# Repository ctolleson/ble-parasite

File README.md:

# b-parasite

## Plant monitor KiCad projects

These are two independent hardware designs. Each has its own `.kicad_pro`, `.kicad_sch`, `.kicad_pcb`, and project libraries.

| Design | KiCad project | Git branch |
| --- | --- | --- |
| **BLE module — Raytac MDBT50Q-1MV2** | [kicad-raytac-plant-monitor/parasite.kicad_pro](kicad-raytac-plant-monitor/parasite.kicad_pro) | `feature-raytac-module-plant-monitor` |
| **Bare MCU — nRF52840-QIAA, AQFN-73** | [kicad-bare-nrf52840/parasite.kicad_pro](https://github.com/ctolleson/ble-parasite/blob/feature-nrf52840-bare-mcu-plant-monitor/kicad-bare-nrf52840/parasite.kicad_pro) | `feature-nrf52840-bare-mcu-plant-monitor` |

The module revision uses 0805 ordinary passives and a 30 mm straight-sided PCB. The bare-MCU project is preserved independently on its branch and in its original checkout. Both use the historical filename `parasite`; identify them by their project directory. The module conversion did not replace the bare-MCU schematic or PCB. The upstream `kicad/` directory below is historical b-parasite reference hardware, not either customized project above.

b-parasite is an open source soil moisture and ambient temperature/humidity/light sensor.

# Features
* Capacitive Soil moisture sensor - see [this blog post](https://rbaron.net/blog/2021/04/05/How-capacitive-soil-moisture-sensors-work.html), [this Twitter thread](https://twitter.com/rbaron_/status/1367182806368071685), and [this post](https://wemakethings.net/2012/09/26/capacitance_measurement/) for nice resources on how they work
* Air temperature and humidity sensor using a [Sensirion's SHTC3](https://sensirion.com/media/documents/643F9C8E/63A5A436/Datasheet_SHTC3.pdf)
* Light sensor using an [ALS-PT19](https://en.everlight.com/wp-content/plugins/ItemRelationship/product_files/pdf/ALS-PT19-315C-L177-TR8_V8.pdf) phototransistor
* Powered by a common CR2032 coin cell, potentially for over two years
* Support for [nRF52840](https://www.nordicsemi.com/products/nrf52840) and [nRF52833](https://www.nordicsemi.com/products/nrf52833) modules
* Open hardware and open source design

# Software
This repository also hosts a few different firmware samples for b-parasite.

|Sample|Description|Extra Documentation|
|---|---|---|
|[samples/ble](./code/samples/ble)|This is the most battle-tested and useful firmware. It periodically reads all sensors and broadcast them via Bluetooth Low Energy (BLE). It works with [Home Assistant](https://www.home-assistant.io/) + [BTHome](https://bthome.io/) out of the box. |[Docs](./code/samples/ble/README.md)|
|[samples/zigbee](./code/samples/zigbee)| An experimental/educational/exploratory basic Zigbee sample built on [nRF Connect + ZBOSS](https://developer.nordicsemi.com/nRF_Connect_SDK/doc/latest/nrf/ug_zigbee.html). It integrates with [Home Assistant](https://www.home-assistant.io/) via [ZHA](https://www.home-assistant.io/integrations/zha) or [Zigbee2MQTT](https://www.zigbee2mqtt.io/). |[Docs](./code/samples/zigbee/README.md)|
|[samples/blinky](./code/samples/blinky)| The classic "Hello, world" |-|
|[samples/soil-read-loop](./code/samples/soil-read-loop)| Reads the soil moisture sensor on a loop. Useful for experimenting and calibrating the sensor. |-|
|[samples/input](./code/samples/input)| Handles button presses. Useful for power profiling GPIO interrupts and testing debouncing for push switches on [boards that have them](https://github.com/rbaron/b-parasite/wiki/Hardware-Versions). |-|

# Documentation
Information about how to order, assemble, build the samples, protect the sensor and flash the firmware is on [the Wiki](https://github.com/rbaron/b-parasite/wiki).

# Repository Organization
* [code/](./code/) - A [`west workspace`](https://docs.zephyrproject.org/latest/develop/west/workspaces.html) containing the common `prstlib` module library and samples, built with Nordic's [nRF Connect SDK](https://www.nordicsemi.com/Products/Development-software/nrf-connect-sdk).
* [kicad/](./kicad/) - KiCad schematic, layout and fabrication files for the printed circuit board (PCB)
* [data/](data/) - data for testing and sensor calibration
* [bridge/](bridge/) - an [ESPHome](https://github.com/esphome/esphome)-based BLE-MQTT bridge
* [case/](case/) - a 3D printable case

# Case

We have three different 3D-printable cases:
1. Original snap-on case - [case/Top.stl](./case/Top.stl), [case/Bottom.stl](./case/Bottom.stl)
2. High airflow - [case/b_parasite_case_high_airflow.stl](./case/b_parasite_case_high_airflow.stl)
3. Mushroom-style - available on [Printables](https://www.printables.com/model/456571-mushroomcap-for-b-parasite-soil-moisture-sensor)
4. b-parasite Hat - available on [Printables](https://www.printables.com/model/901220-waterproof-case-for-b-parasite-soil-moisture-air-s)

# Accessories

Designs and hardware to help you, when building your own:
1. Desk holder for b-parasites [Printables](https://www.printables.com/de/model/566974-b-parasite-holder)

# License
The hardware and associated design files are released under the [Creative Commons CC BY-SA 4.0 license](https://creativecommons.org/licenses/by-sa/4.0/).
The code is released under the [MIT license](https://opensource.org/licenses/MIT).

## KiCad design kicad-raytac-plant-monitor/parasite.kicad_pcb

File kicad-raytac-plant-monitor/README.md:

# Raytac nRF52840 plant monitor — MODULE-B

Independent KiCad project using Raytac MDBT50Q-1MV2 with its integrated chip antenna. Open `parasite.kicad_pro` in KiCad 10. The prior bare-MCU design remains in its original branch.

## Interfaces

- **J1:** 2 × 5, 1.27 mm Cortex SWD header for a J-Link probe or compatible adapter. Pin 1: target +3V0/VTref; 2: SWDIO; 3: GND; 4: SWDCLK; 5: GND; 6: SWO (P1.00); 7: NC/key; 8: NC; 9: GND detect; 10: nRESET. Power the target from its battery; VTref is a voltage reference, not a probe power input. Check cable orientation against pin 1 before connecting. Header pin 7 is electrically unused; remove it if required by a keyed cable.
- **J2:** 1 × 4, 2.54 mm I2C expansion header. Pins 1–4: +3V0, GND, SDA/P0.24, SCL/P0.13. Shared with the SHTC3 and existing 10 kΩ pull-ups. Use short wiring and do not apply 5 V.
- **J3:** 1 × 2, 2.54 mm external NFC antenna header. Pin 1: NFC1/P0.09; pin 2: NFC2/P0.10. An external antenna and matching/tuning appropriate to its inductance are required. The module's chip antenna is for 2.4 GHz BLE, not NFC.

## Hardware

- CR2032 supply; module VDD and VDDH share +3V0, REG0 bypassed. DCCH is unused. VBUS is grounded and USB data pins are unused, following Raytac's no-USB application circuit.
- Module contains the 32 MHz crystal, RF matching and regulator inductors. External 32.768 kHz crystal retained.
- All seven ordinary host resistors, all six capacitors and D2 use standard imperial **0805** (2.0 × 1.25 mm nominal bodies). The Raytac module, sensors, crystal, diode, transistor, switches and connectors retain their required packages. Values are preserved; 0805 manufacturer part numbers and electrical ratings are recorded in the schematic and PCB fields. Inventory has not been rechecked for this revision.
- **30.0 × 126.4 mm** board with straight, parallel vertical sides and a 45° tapered bottom tip inspired by the original b-parasite. Components are above the soil limit; the CR2032 holder is on the back.
- Four copper layers; 0.15 mm minimum signal width, 0.125 mm clearance, ordinary through vias with 0.60 mm copper / 0.30 mm drill. No blind/buried vias or microvias.
- Antenna at the top board edge with an all-layer copper/tracks/vias keepout across the head. Keep metal, the battery, cables and enclosure hardware away from the antenna.
- Soil probe electrode and surrounding ground remain covered by solder mask. A GND through via near the tip connects the front and back probe ground pours.

## Validation status

KiCad 10 native ERC: **0 violations**. Native DRC: **0 violations, 0 unconnected items**. Independent comparison of the native schematic netlist and saved PCB: **133/133 pad nets match**, including all 40 intentional no-connect pads. Saved reports and previews are in `review/`.

MCP PCB quality gate passes. Other MCP heuristics flag native no-connect net names, wire-interior pin joins, opposing-side placement and module-center-to-cap distance; these are reviewed in `review/REVIEW.md`. They are not represented as blanket gate passes.

**Manufacturing status: needs engineering review; not a manufacturing release.** Select exact connector SKUs and confirm their land patterns/cable fit before procurement. J1 currently uses KiCad’s generic 2×5 1.27 mm SMT pin-header footprint. Check the assembly process for the module and underside battery holder. A new manufacturing package and quotation are needed for this revision. Firmware must use the new GPIO assignments and configure NFC/SWO as required. Verify soil calibration, sensor behavior, sleep current, crystal start-up, BLE range and NFC antenna tuning on hardware.

## References

- [Raytac module specification](https://www.raytac.com/tw/download/index.php?index_id=24)
- [Nordic nRF52840 pin assignments](https://docs.nordicsemi.com/r/bundle/ps_nrf52840/page/pin.html)

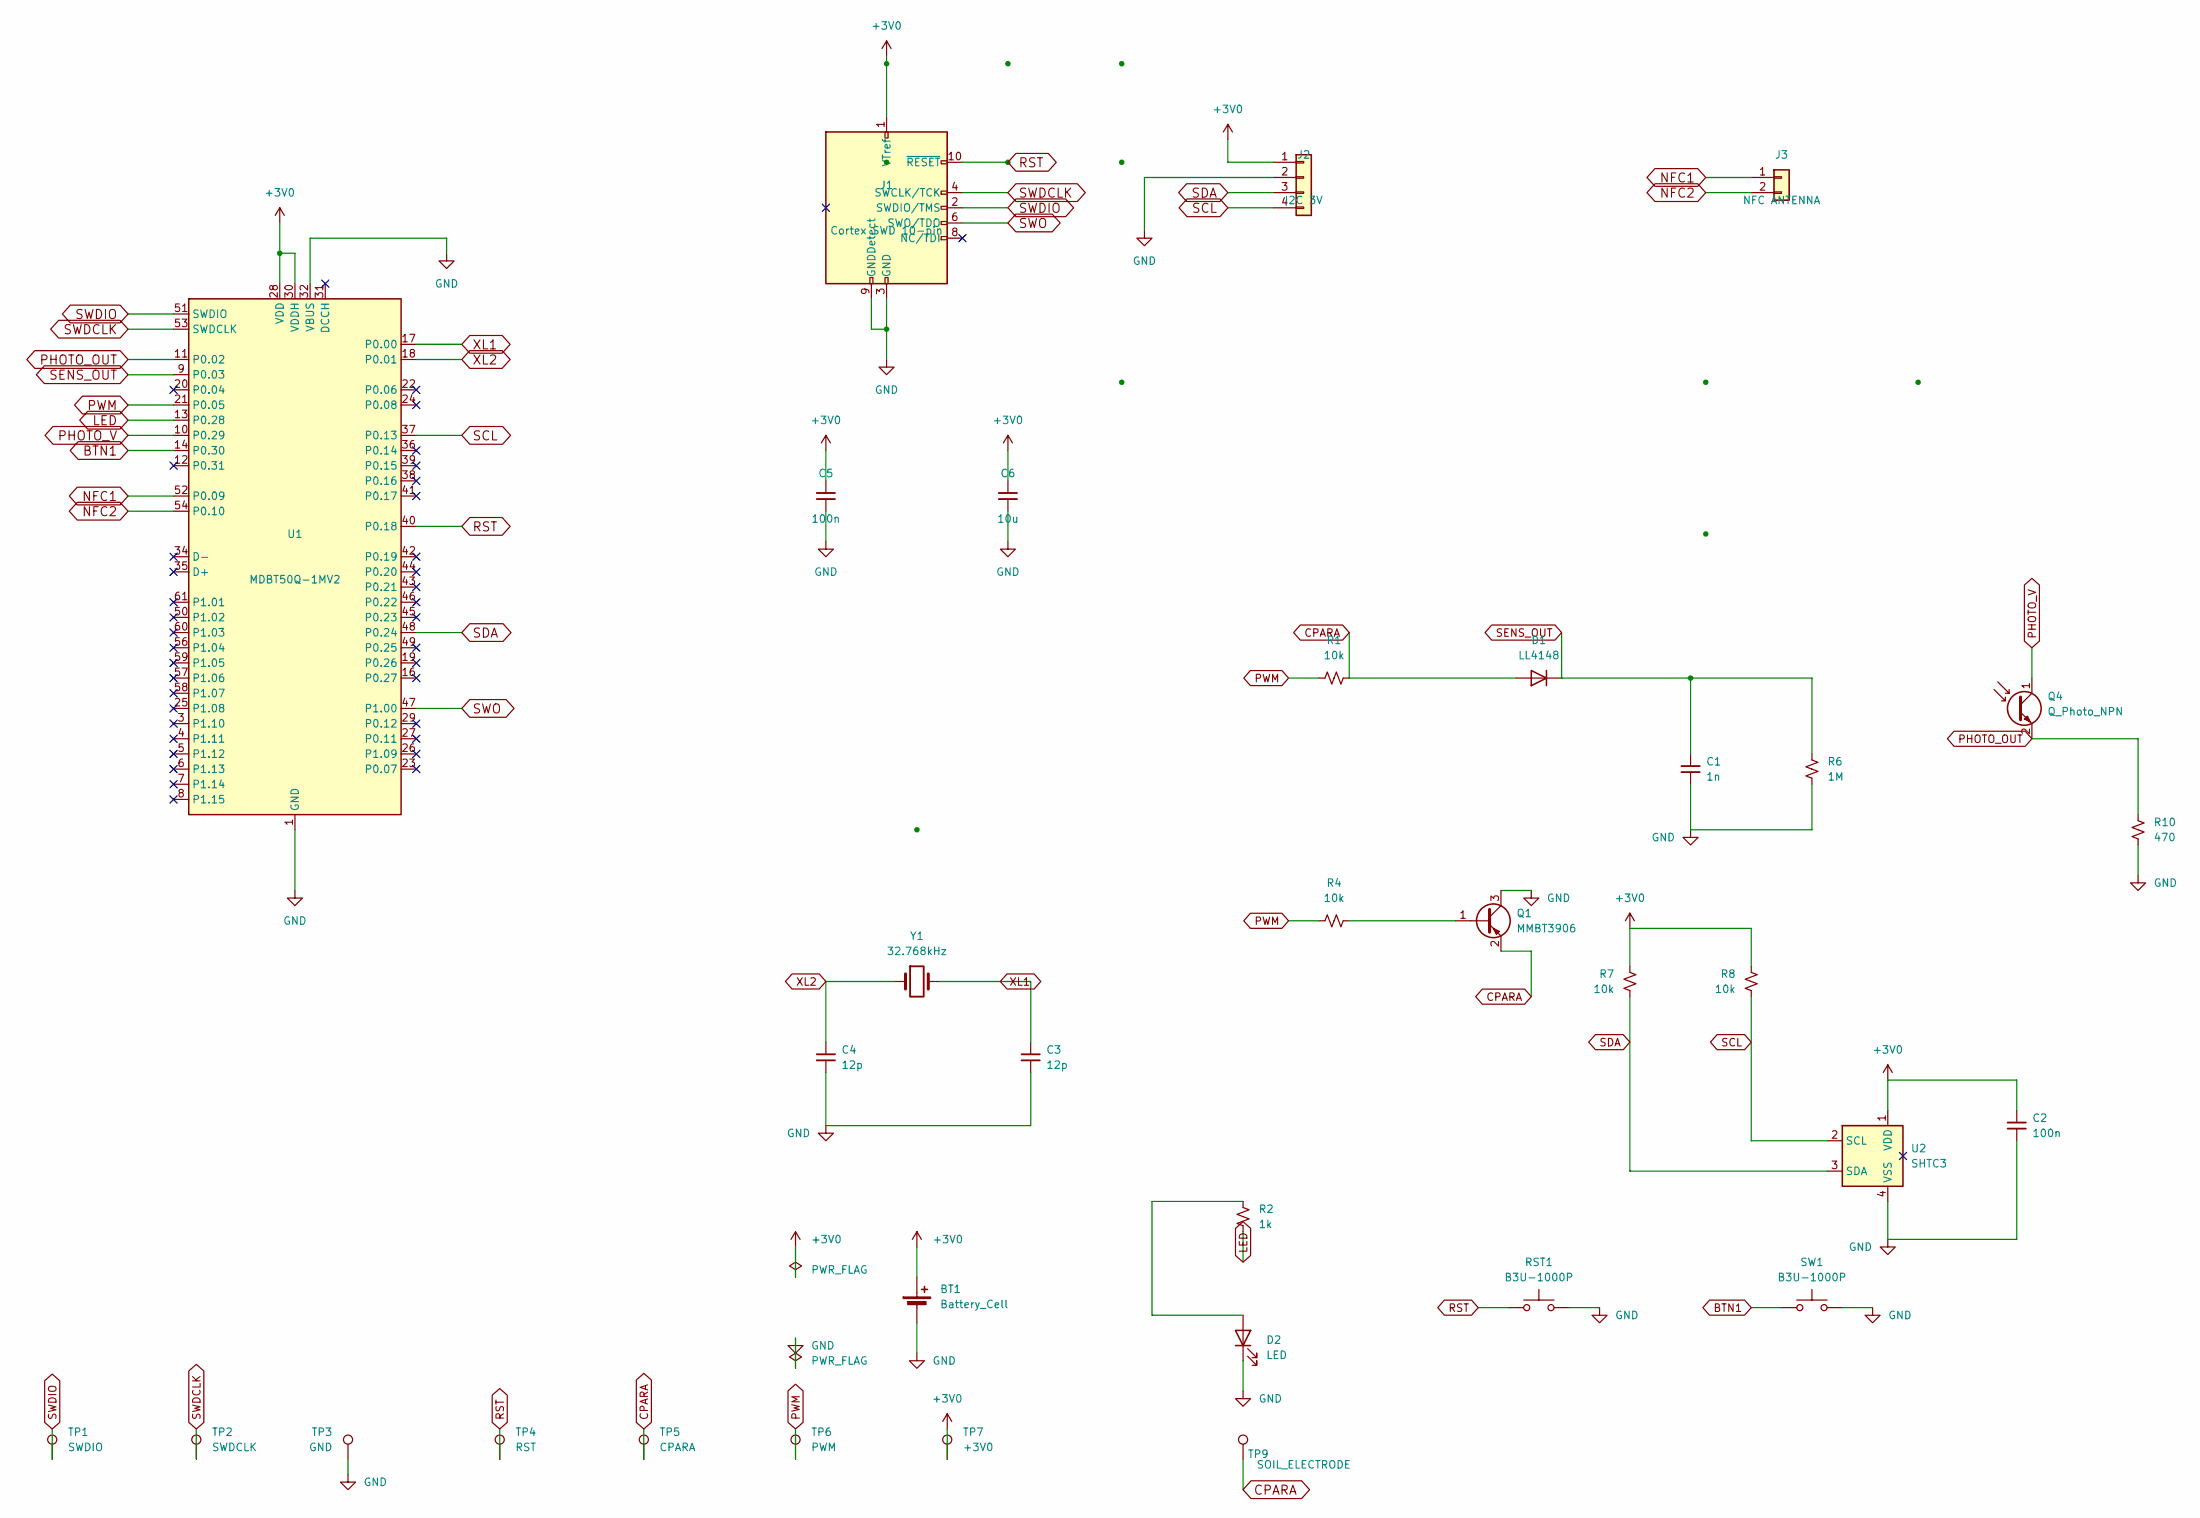
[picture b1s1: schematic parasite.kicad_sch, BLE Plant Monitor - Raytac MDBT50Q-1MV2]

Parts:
BT1: Battery_Cell; BatteryHolder_Keystone_1060_NoBodySilk; MPN 1060; LCSC C5370859
C1: 1n; C_0805_2012Metric; Voltage 50V; MPN C0805C102J5GACTU
C2, C5: 100n; C_0805_2012Metric; Voltage 50V; MPN C0805C104K5RACTU
C3, C4: 12p; C_0805_2012Metric; Voltage 50V; MPN C0805C120J5GACTU
C6: 10u; C_0805_2012Metric; Voltage 16V; MPN GRM21BR61C106KE15L
D1: LL4148; D_MiniMELF; MPN LL4148; LCSC C9808
D2: LED; LED_0805_2012Metric; MPN AP2012SURCK
J1: Cortex SWD 10-pin; PinHeader_2x05_P1.27mm_Vertical_SMD
J2: I2C 3V; PinHeader_1x04_P2.54mm_Vertical
J3: NFC ANTENNA; PinHeader_1x02_P2.54mm_Vertical
Q1: MMBT3906; SOT-23; MPN MMBT3906LT1G; DigiKey MMBT3906LT1GOSCT-ND
Q4: Q_Photo_NPN; TR8; MPN ALS-PT19-315C/L177/TR8; LCSC C146233
R1, R4, R7, R8: 10k; R_0805_2012Metric; MPN RC0805FR-0710KL
R2: 1k; R_0805_2012Metric; MPN RC0805FR-071KL
R6: 1M; R_0805_2012Metric; MPN RC0805FR-071ML
R10: 470; R_0805_2012Metric; MPN RC0805FR-07470RL
RST1: B3U-1000P; SW_B3U-1000P; MPN B3U-1000P; LCSC C231329
SW1: B3U-1000P; SW_B3U-1000P; MPN B3U-1000P; LCSC C231329
TP1: SWDIO; TestPoint_Pad_D1.0mm
TP2: SWDCLK; TestPoint_Pad_D1.0mm
TP3: GND; TestPoint_Pad_D1.0mm
TP4: RST; TestPoint_Pad_D1.0mm
TP5: CPARA; TestPoint_Pad_D1.0mm
TP6: PWM; TestPoint_Pad_D1.0mm
TP7: +3V0; TestPoint_Pad_D1.0mm
TP9: SOIL_ELECTRODE; Soil_Electrode_Endpoint_Covered
U1: MDBT50Q-1MV2; Raytac_MDBT50Q; MPN MDBT50Q-1MV2
U2: SHTC3; Sensirion_DFN-4-1EP_2x2mm_P1mm_EP0.7x1.6mm; MPN SHTC3-TR-2.5KS; LCSC C194656
Y1: 32.768kHz; Crystal_SMD_3215-2Pin_3.2x1.5mm; MPN STDMUA9-32.768K; LCSC C519280

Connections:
+3V0: BT1.1 (+), C2.1, C5.1, C6.1, J1.1 (VTref), J2.1, R7.2, R8.1, TP7.1 (1_1), U1.28 (VDD), U1.30 (VDDH), U2.1 (VDD)
BTN1: SW1.1, U1.14 (P0.30)
CPARA: D1.2 (A), Q1.2 (E), R1.2, TP5.1 (1_1), TP9.1 (1_1)
GND: BT1.2 (-), C1.2, C2.2, C3.1, C4.2, C5.2, C6.2, D2.1 (K), J1.3 (GND), J1.5 (GND), J1.9 (GNDDetect), J2.2, Q1.3 (C), R6.2, R10.1, RST1.2, SW1.2, TP3.1 (1_1), U1.1 (GND), U1.2 (GND), U1.15 (GND), U1.32 (VBUS), U1.33 (GND), U1.55 (GND), U2.4 (VSS)
LED: R2.2, U1.13 (P0.28)
NFC1: J3.1, U1.52 (P0.09)
NFC2: J3.2, U1.54 (P0.10)
unnamed: D2.2 (A), R2.1
unnamed: Q1.1 (B), R4.1
PHOTO_OUT: Q4.2 (E), R10.2, U1.11 (P0.02)
PHOTO_V: Q4.1 (C), U1.10 (P0.29)
PWM: R1.1, R4.2, TP6.1 (1_1), U1.21 (P0.05)
RST: J1.10 (~RESET), RST1.1, TP4.1 (1_1), U1.40 (P0.18)
SCL: J2.4, R8.2, U1.37 (P0.13), U2.2 (SCL)
SDA: J2.3, R7.1, U1.48 (P0.24), U2.3 (SDA)
SENS_OUT: C1.1, D1.1 (K), R6.1, U1.9 (P0.03)
SWDCLK: J1.4 (SWCLK/TCK), TP2.1 (1_1), U1.53 (SWDCLK)
SWDIO: J1.2 (SWDIO/TMS), TP1.1 (1_1), U1.51 (SWDIO)
SWO: J1.6 (SWO/TDO), U1.47 (P1.00)
XL1: C3.2, U1.17 (P0.00), Y1.2
XL2: C4.1, U1.18 (P0.01), Y1.1

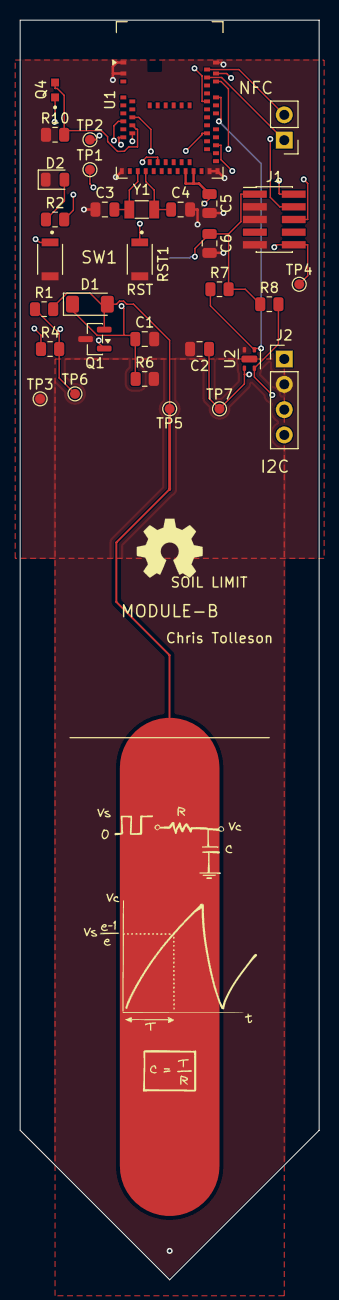
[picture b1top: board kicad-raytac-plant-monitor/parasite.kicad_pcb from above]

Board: 4 copper layers, 30.0 x 126.4 mm, 34 parts (1 on the bottom side), 21 nets.

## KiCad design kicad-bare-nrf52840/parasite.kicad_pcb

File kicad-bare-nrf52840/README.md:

# Bare nRF52840 b-parasite

Open `parasite.kicad_pro` with KiCad 10. Read [DESIGN_BRIEF.md](DESIGN_BRIEF.md) for SWD programming, JLCPCB process requirements, validation and prototype limitations. This directory contains the new bare-IC revision; the original module design is retained separately.

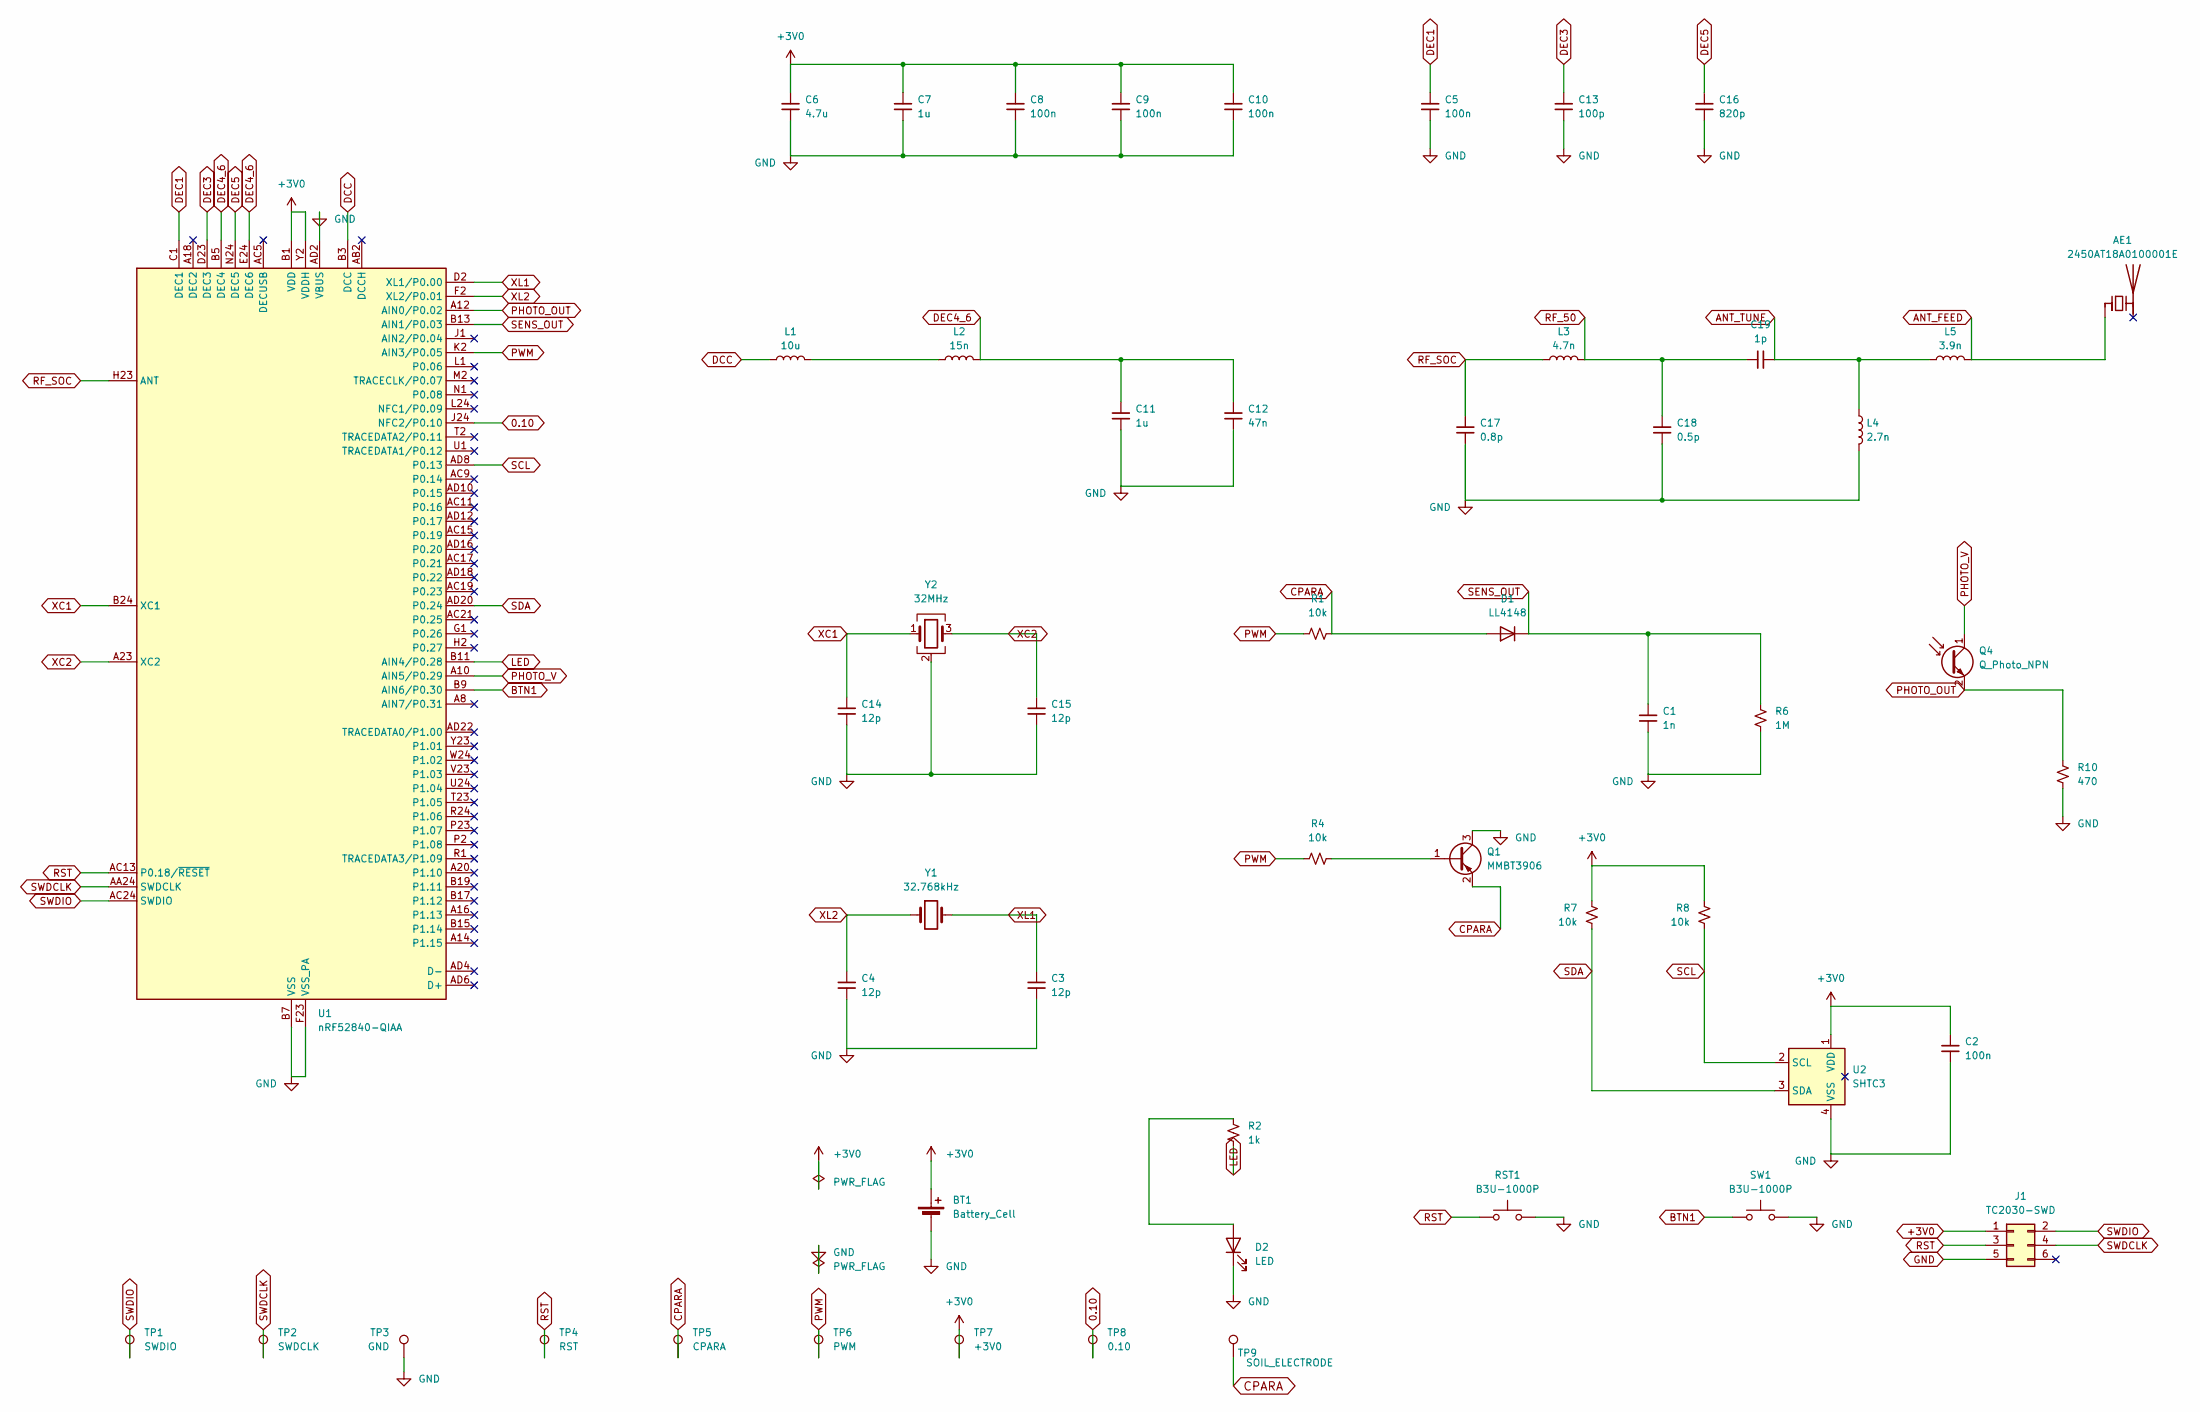
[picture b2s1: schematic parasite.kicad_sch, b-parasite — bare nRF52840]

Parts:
AE1: 2450AT18A0100001E; Johanson_2450AT18x100; MPN 2450AT18A0100001E; DigiKey 712-2450AT18A0100001ECT-ND
BT1: Battery_Cell; BatteryHolder_Keystone_1060_NoBodySilk; MPN 1060; LCSC C5370859
C1: 1n; C_0402_1005Metric; MPN CC0402KRX7R9BB102; DigiKey 311-1036-1-ND
C2, C5, C8, C9, C10: 100n; C_0402_1005Metric; MPN CC0402KRX7R7BB104; DigiKey 311-1338-1-ND
C3, C4, C14, C15: 12p; C_0402_1005Metric; MPN CC0402JRNPO9BN120; DigiKey 311-1016-1-ND
C6: 4.7u; C_0603_1608Metric; Voltage 16V; Tolerance 10%; MPN GRM188R61C475KE11J; DigiKey 490-GRM188R61C475KE11JCT-ND
C7, C11: 1u; C_0402_1005Metric; MPN CL05A105KA5NQNC; LCSC C52923
C12: 47n; C_0402_1005Metric; MPN CC0402KRX7R8BB473; DigiKey 311-1717-1-ND
C13: 100p; C_0402_1005Metric; MPN CC0402JRNPO9BN101; DigiKey 311-1024-1-ND
C16: 820p; C_0402_1005Metric; MPN CL05C821JB5NNNC; LCSC C307452
C17: 0.8p; C_0402_1005Metric; MPN GRM1555C1HR80BA01D; LCSC C76988
C18: 0.5p; C_0402_1005Metric; MPN GJM1555C1HR50WB01D; LCSC C76912
C19: 1p; C_0402_1005Metric; MPN GRM1555C1H1R0BA01D; DigiKey 490-6206-1-ND
D1: LL4148; D_MiniMELF; MPN LL4148; LCSC C9808
D2: LED; LED_0603_1608Metric; MPN LTST-C190KRKT; DigiKey 160-1436-1-ND
J1: TC2030-SWD; Tag-Connect_TC2030-IDC-NL_2x03_P1.27mm_Vertical
L1: 10u; L_0603_1608Metric; MPN MLZ1608M100WTD25; LCSC C2047264
L2: 15n; L_0402_1005Metric; MPN LQG15HS15NJ02D; LCSC C86059
L3: 4.7n; L_0402_1005Metric; MPN LQG15HS4N7B02D; LCSC C162543
L4: 2.7n; L_0402_1005Metric; MPN LQG15HS2N7S02D; LCSC C77108
L5: 3.9n; L_0402_1005Metric; MPN LQG15HS3N9S02D; DigiKey 490-2617-1-ND
Q1: MMBT3906; SOT-23; MPN MMBT3906LT1G; DigiKey MMBT3906LT1GOSCT-ND
Q4: Q_Photo_NPN; TR8; MPN ALS-PT19-315C/L177/TR8; LCSC C146233
R1, R4, R7, R8: 10k; R_0402_1005Metric; MPN RC0402FR-0710KL; DigiKey 311-10.0KLRCT-ND
R2: 1k; R_0402_1005Metric; MPN RC0402FR-071KL; DigiKey 311-1.00KLRCT-ND
R6: 1M; R_0402_1005Metric; MPN RC0402FR-071ML; DigiKey 311-1.00MLRCT-ND
R10: 470; R_0402_1005Metric; MPN RC0402FR-07470RL; DigiKey 311-470LRCT-ND
RST1: B3U-1000P; SW_B3U-1000P; MPN B3U-1000P; LCSC C231329
SW1: B3U-1000P; SW_B3U-1000P; MPN B3U-1000P; LCSC C231329
TP1: SWDIO; TestPoint_Pad_D1.0mm
TP2: SWDCLK; TestPoint_Pad_D1.0mm
TP3: GND; TestPoint_Pad_D1.0mm
TP4: RST; TestPoint_Pad_D1.0mm
TP5: CPARA; TestPoint_Pad_D1.0mm
TP6: PWM; TestPoint_Pad_D1.0mm
TP7: +3V0; TestPoint_Pad_D1.0mm
TP8: 0.10; TestPoint_Pad_D1.0mm
TP9: SOIL_ELECTRODE; Soil_Electrode_Endpoint_Covered
U1: nRF52840-QIAA; Nordic_AQFN-73-1EP_7x7mm_P0.5mm; MPN NRF52840-QIAA-R; LCSC C190794
U2: SHTC3; Sensirion_DFN-4-1EP_2x2mm_P1mm_EP0.7x1.6mm; MPN SHTC3-TR-2.5KS; LCSC C194656
Y1: 32.768kHz; Crystal_SMD_3215-2Pin_3.2x1.5mm; MPN STDMUA9-32.768K; LCSC C519280
Y2: 32MHz; Crystal_SMD_2016-4Pin_2.0x1.6mm; MPN CX2016DB32000D0FLJCC

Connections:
0.10: TP8.1 (1_1), U1.J24 (NFC2/P0.10)
+3V0: BT1.1 (+), C2.1, C6.1, C7.1, C8.1, C9.1, C10.1, J1.1, R7.2, R8.1, TP7.1 (1_1), U1.A22 (VDD), U1.AD14 (VDD), U1.AD23 (VDD), U1.B1 (VDD), U1.W1 (VDD), U1.Y2 (VDDH), U2.1 (VDD)
ANT_FEED: AE1.1 (FEED_1), L5.2
ANT_TUNE: C19.2, L4.1, L5.1
BTN1: SW1.1, U1.B9 (AIN6/P0.30)
CPARA: D1.2 (A), Q1.2 (E), R1.2, TP5.1 (1_1), TP9.1 (1_1)
DCC: L1.1, U1.B3 (DCC)
DEC1: C5.1, U1.C1 (DEC1)
DEC3: C13.1, U1.D23 (DEC3)
DEC4_6: C11.1, C12.1, L2.2, U1.B5 (DEC4), U1.E24 (DEC6)
DEC5: C16.1, U1.N24 (DEC5)
GND: BT1.2 (-), C1.2, C2.2, C3.1, C4.2, C5.2, C6.2, C7.2, C8.2, C9.2, C10.2, C11.2, C12.2, C13.2, C14.2, C15.2, C16.2, C17.2, C18.2, D2.1 (K), J1.5, L4.2, Q1.3 (C), R6.2, R10.1, RST1.2, SW1.2, TP3.1 (1_1), U1.AD2 (VBUS), U1.B7 (VSS), U1.EP (VSS), U1.F23 (VSS_PA), U2.4 (VSS), Y2.2 (G), Y2.4 (G)
LED: R2.2, U1.B11 (AIN4/P0.28)
unnamed: D2.2 (A), R2.1
unnamed: L1.2, L2.1
unnamed: Q1.1 (B), R4.1
PHOTO_OUT: Q4.2 (E), R10.2, U1.A12 (AIN0/P0.02)
PHOTO_V: Q4.1 (C), U1.A10 (AIN5/P0.29)
PWM: R1.1, R4.2, TP6.1 (1_1), U1.K2 (AIN3/P0.05)
RF_50: C18.1, C19.1, L3.2
RF_SOC: C17.1, L3.1, U1.H23 (ANT)
RST: J1.3, RST1.1, TP4.1 (1_1), U1.AC13 (P0.18/~RESET)
SCL: R8.2, U1.AD8 (P0.13), U2.2 (SCL)
SDA: R7.1, U1.AD20 (P0.24), U2.3 (SDA)
SENS_OUT: C1.1, D1.1 (K), R6.1, U1.B13 (AIN1/P0.03)
SWDCLK: J1.4, TP2.1 (1_1), U1.AA24 (SWDCLK)
SWDIO: J1.2, TP1.1 (1_1), U1.AC24 (SWDIO)
XC1: C14.1, U1.B24 (XC1), Y2.1
XC2: C15.1, U1.A23 (XC2), Y2.3
XL1: C3.2, U1.D2 (XL1/P0.00), Y1.2
XL2: C4.1, U1.F2 (XL2/P0.01), Y1.1

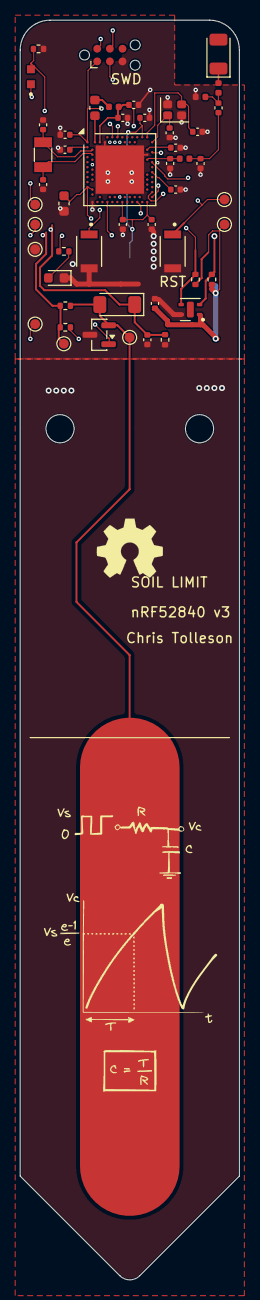
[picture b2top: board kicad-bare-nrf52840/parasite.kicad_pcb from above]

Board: 4 copper layers, 22.0 x 126.4 mm, 53 parts (1 on the bottom side), 31 nets.

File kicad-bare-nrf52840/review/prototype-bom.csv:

"Reference","Value","Footprint","MPN","LCSC","Dielectric","Assembly_note","Qty"
"AE1","2450AT18B0100001E","RF_Antenna:Johanson_2450AT18x100","2450AT18B0100001E","","","Tuning network starts at evaluation-board values; VNA tuning required","1"
"BT1","Battery_Cell","Battery:BatteryHolder_Keystone_1060_1x2032","1060","","","","1"
"C1","1n","Capacitor_SMD:C_0402_1005Metric","","C1523","","","1"
"C2","100n","Capacitor_SMD:C_0402_1005Metric","","C1525","","","1"
"C3","12p","Capacitor_SMD:C_0402_1005Metric","","C1547","","","1"
"C4","12p","Capacitor_SMD:C_0402_1005Metric","","C1547","","","1"
"C5","100n","Capacitor_SMD:C_0402_1005Metric","","","","","1"
"C6","4.7u","Capacitor_SMD:C_0402_1005Metric","","","","","1"
"C7","1u","Capacitor_SMD:C_0402_1005Metric","","","","","1"
"C8","100n","Capacitor_SMD:C_0402_1005Metric","","","","","1"
"C9","100n","Capacitor_SMD:C_0402_1005Metric","","","","","1"
"C10","100n","Capacitor_SMD:C_0402_1005Metric","","","","","1"
"C11","1u","Capacitor_SMD:C_0402_1005Metric","","","","","1"
"C12","47n","Capacitor_SMD:C_0402_1005Metric","","","","","1"
"C13","100p","Capacitor_SMD:C_0402_1005Metric","","","","","1"
"C14","12p","Capacitor_SMD:C_0402_1005Metric","","","C0G/NP0","","1"
"C15","12p","Capacitor_SMD:C_0402_1005Metric","","","C0G/NP0","","1"
"C16","820p","Capacitor_SMD:C_0402_1005Metric","","","","Optional for Fxx and later; fit for earlier builds","1"
"C17","0.8p","Capacitor_SMD:C_0402_1005Metric","","","C0G/NP0","","1"
"C18","0.5p","Capacitor_SMD:C_0402_1005Metric","","","C0G/NP0","","1"
"C19","1.2p","Capacitor_SMD:C_0402_1005Metric","","","C0G/NP0","","1"
"D1","LL4148","Diode_SMD:D_MiniMELF","","C9808","","","1"
"D2","LED","LED_SMD:LED_0603_1608Metric","","C2286","","","1"
"J1","TC2030-SWD","Connector:Tag-Connect_TC2030-IDC-NL_2x03_P1.27mm_Vertical","","","","","1"
"L1","10u","Inductor_SMD:L_0603_1608Metric","MLZ1608M100WTD25","","","","1"
"L2","15n","Inductor_SMD:L_0402_1005Metric","LQG15HS15NJ02D","","","","1"
"L3","4.7n","Inductor_SMD:L_0402_1005Metric","LQG15HS4N7B02D","","","","1"
"L4","2.7n","Inductor_SMD:L_0402_1005Metric","","","","","1"
"L5","3.3n","Inductor_SMD:L_0402_1005Metric","","","","","1"
"Q1","MMBT3906","Package_TO_SOT_SMD:SOT-23","","C2910191","","","1"
"Q4","Q_Photo_NPN","snapeda:TR8","","C146233","","","1"
"R1","10k","Resistor_SMD:R_0402_1005Metric","","C25744","","","1"
"R2","1k","Resistor_SMD:R_0402_1005Metric","","C11702","","","1"
"R4","10k","Resistor_SMD:R_0402_1005Metric","","C25744","","","1"
"R6","1M","Resistor_SMD:R_0402_1005Metric","","C26083","","","1"
"R7","10k","Resistor_SMD:R_0402_1005Metric","","C25744","","","1"
"R8","10k","Resistor_SMD:R_0402_1005Metric","","C25744","","","1"
"R10","470","Resistor_SMD:R_0402_1005Metric","","C25117","","","1"
"RST1","B3U-1000P","snapeda:SW_B3U-1000P","","C231329","","","1"
"SW1","B3U-1000P","snapeda:SW_B3U-1000P","","C231329","","","1"
"TP1","SWDIO","TestPoint:TestPoint_Pad_D1.0mm","","","","","1"
"TP2","SWDCLK","TestPoint:TestPoint_Pad_D1.0mm","","","","","1"
"TP3","GND","TestPoint:TestPoint_Pad_D1.0mm","","","","","1"
"TP4","RST","TestPoint:TestPoint_Pad_D1.0mm","","","","","1"
"TP5","CPARA","TestPoint:TestPoint_Pad_D1.0mm","","","","","1"
"TP6","PWM","TestPoint:TestPoint_Pad_D1.0mm","","","","","1"
"TP7","+3V0","TestPoint:TestPoint_Pad_D1.0mm","","","","","1"
"TP8","0.10","TestPoint:TestPoint_Pad_D1.0mm","","","","","1"
"U1","nRF52840-QIAA","Package_DFN_QFN:Nordic_AQFN-73-1EP_7x7mm_P0.5mm","nRF52840-QIAA","","","","1"
"U2","SHTC3","kicad:Sensirion_DFN-4-1EP_2x2mm_P1mm_EP0.7x1.6mm","","C194656","","","1"
"Y1","32.768kHz","Crystal:Crystal_SMD_3215-2Pin_3.2x1.5mm","NX3215SA-32.768K-STD-MUA-9","C32346","","","1"
"Y2","32MHz","Crystal:Crystal_SMD_2016-4Pin_2.0x1.6mm","MP12308","","","","1"

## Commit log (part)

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2026-02-13 testing commit.
2026-02-13 Added a copy of the KiCAD project to change the circuit board.
2026-02-13 Created a new KiCad project and renamed the project, put it in a new folder.
2026-02-13 removed unused kicad "experimental" project.

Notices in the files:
kicad-bare-nrf52840/parasite.kicad_pcb:
Derived from rbaron/b-parasite; hardware CC BY-SA 4.0
